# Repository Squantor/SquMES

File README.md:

# SquMES (Squantor Modular Electronics System)
This repository contains a modular system for electronics projects. 
This system comprises of a backplane and some modules, the modules are inserted into the backplane. Instead of the [ModEleSys](https://github.com/Squantor/ModEleSys) where everything is horizontal, the SquMES is vertical, this makes the backplane not so big and a bit more space efficient but the modules also have more PCB surface allowing more complex projects.

WARNING: This is still a work in progress, check back later if you are interested.

## Structure
* [electronics](electronics/README.md) contains electronics schematics and PCB drawings using Kicad
* [mechanical](mechanical/README.md) contains all the CAD drawings, mostly 3d printable objects.
* [documentation](documentation/README.md) contains more in depth information and examples using this system.
## Cloning
This repository makes use of submodules, use ```git clone --recurse-submodules https://github.com/Squantor/generic_project_template.git``` to clone everything in one go.

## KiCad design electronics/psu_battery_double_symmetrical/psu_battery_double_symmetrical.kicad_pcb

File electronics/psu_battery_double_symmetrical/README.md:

# SquMES Dual 9V battery symmetrical Powersupply
Simple symmetrical powersupply based on two batteries, has a low battery and power led indicator.
## TODO's
Still some things need to be done:
* Review with one night in between
* Produce at [OSHPARK](https://oshpark.com/)
* Assemble
* Test & characterise
* update Readme.md with pictures and BOM

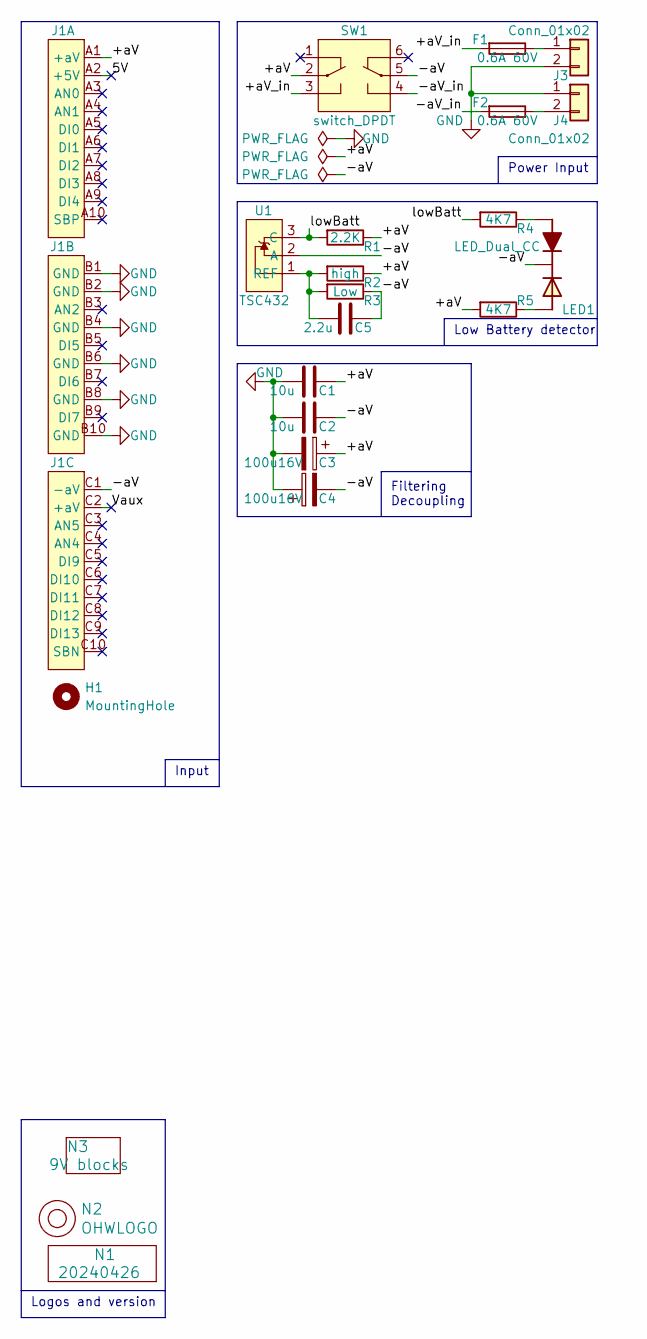
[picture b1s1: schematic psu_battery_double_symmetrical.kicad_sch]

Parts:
C1, C2: 10u; C_1206_0805
C3, C4: 100u16V; C-025-065-elco
C5: 2.2u; C_0805
F1, F2: 0.6A 60V; F_1812-bourns
H1: MountingHole; MountingHole_2.7mm_M2.5_Pad
J1: DIN41612_C3_3x10_Male_Horizontal_THT
J3, J4: Conn_01x02; JST_XH_B2B-XH-A_1x02_P2.50mm_Vertical
LED1: LED_Dual_CC; LED_DUAL_TH245_90deg
N1: 20240426; Label_Generic
N2: OHWLOGO; OSHW-Symbol_6.7x6mm_SilkScreen
N3: 9V blocks; battery_holder_9v_stacked
R1: 2.2K; R_0603_hand
R2: high; R_0603_hand
R3: Low; R_0603_hand
R4, R5: 4K7; R_0603_hand
SW1: switch_DPDT; PS-22F02
U1: TSC432; TO-92L_Inline_Wide

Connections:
/5V: J1.A2 (+5V)
/+aV: C1.2, C3.1, J1.A1 (+aV), R1.1, R2.1, R5.2, SW1.2 (SW1_C1)
/+aV_in: F1.2, SW1.3 (SW1_P2)
/-aV: C2.2, C4.2, C5.2, J1.C1 (-aV), LED1.2 (C), R3.1, SW1.5 (SW2_C1), U1.2 (A)
/-aV_in: F2.2, SW1.4 (SW2_P2)
/Vaux: J1.C2 (+aV)
/lowBatt: R1.2, R4.2, U1.3 (C)
GND: C1.1, C2.1, C3.2, C4.1, J1.B1 (GND), J1.B2 (GND), J1.B4 (GND), J1.B6 (GND), J1.B8 (GND), J1.B10 (GND), J3.2, J4.1
unnamed: F1.1, J3.1
unnamed: F2.1, J4.2
unnamed: LED1.1 (A1), R4.1
unnamed: LED1.3 (A2), R5.1
unnamed: C5.1, R2.2, R3.2, U1.1 (REF)

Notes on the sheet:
Filtering Decoupling
Input
Logos and version
Power Input
Low Battery detector

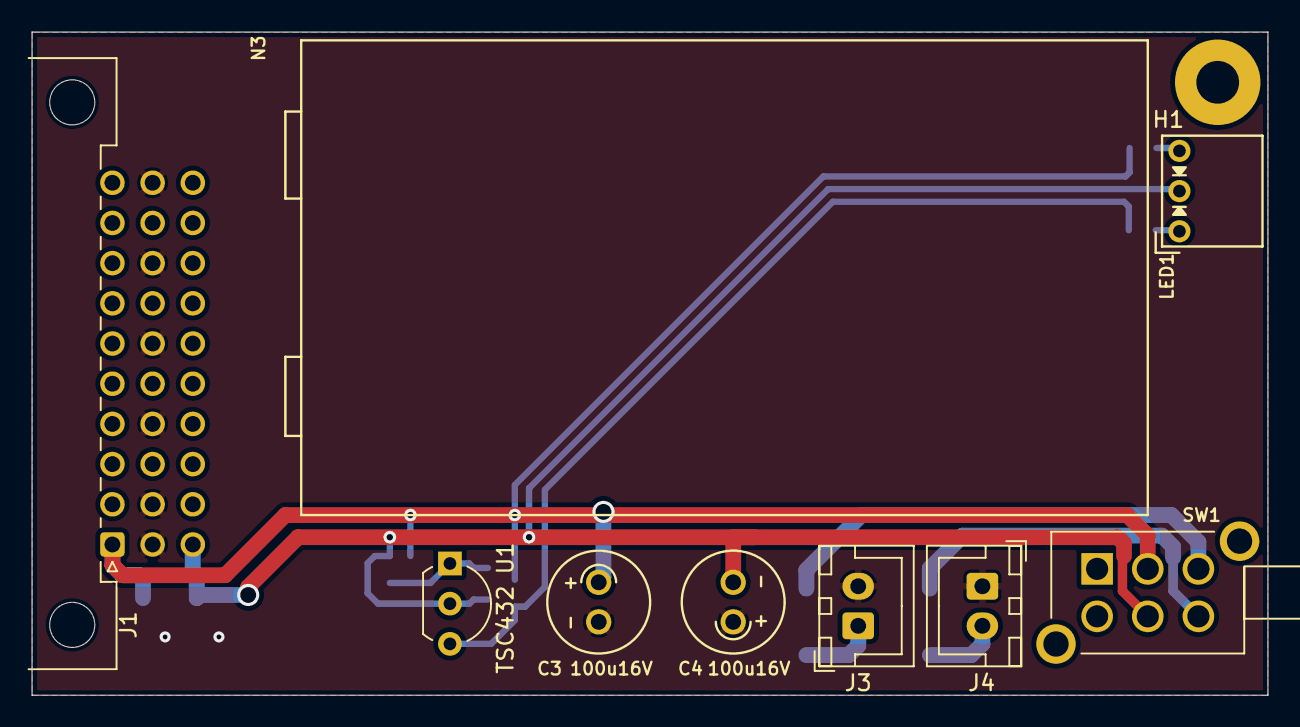
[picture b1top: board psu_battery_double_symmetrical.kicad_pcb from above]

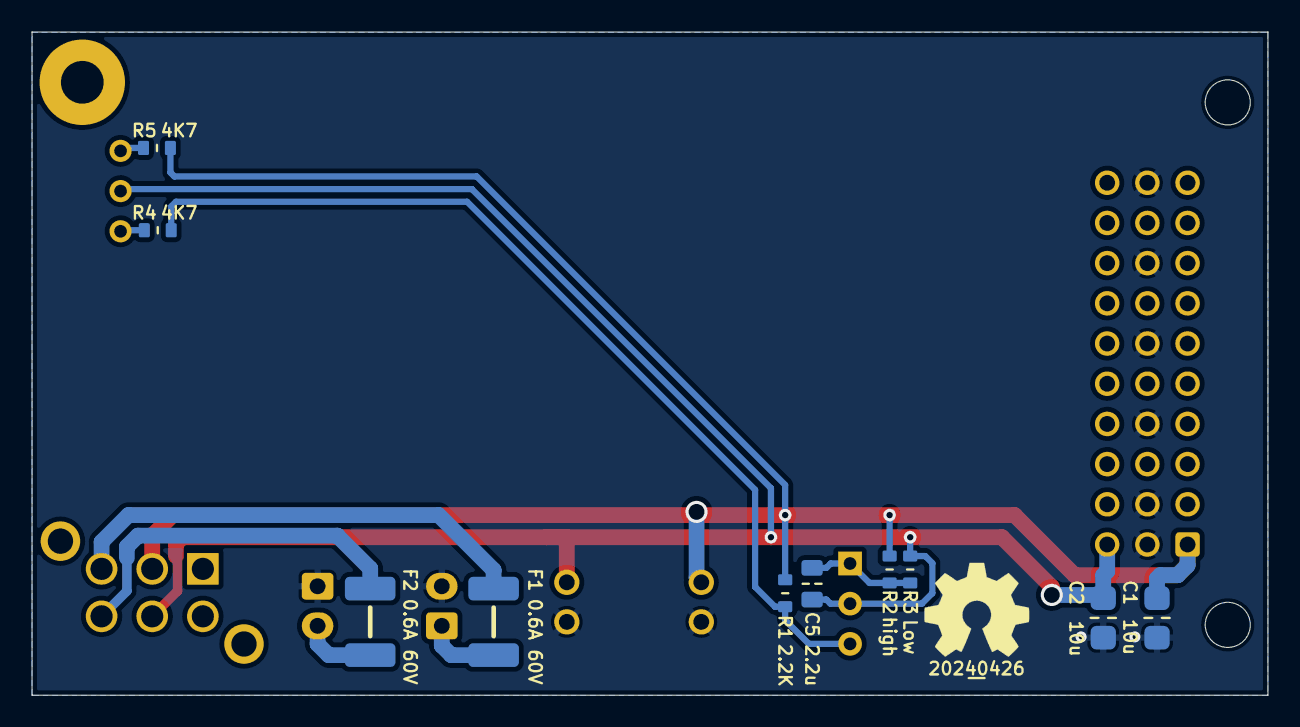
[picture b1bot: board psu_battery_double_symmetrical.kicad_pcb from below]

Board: 2 copper layers, 78.1 x 41.9 mm, 22 parts (12 on the bottom side), 11 nets.

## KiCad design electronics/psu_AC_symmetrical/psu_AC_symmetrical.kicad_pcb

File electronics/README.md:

# SquMES electronics
The backplanes and modules of the ModEleSys are stored here.
Backplanes are prefixed with ```bp``` and some extra description.
Mmodules are prefixed with ```mod``` and size in the form of ```W?``` where ? would be the size indicator. For example ```mod_W2_PSU_symmetrical``` is a module of 2 width units that contains a symmetric powersupply. One width unit is 14mm.
## Backplanes
* 30 pin DIN 41612 connector backplane for 10x10x5 cm extruded aluminium boxes
* 30 pin DIN 41612 connector backplane for larger cm extruded aluminium boxes
* 48 pin DIN 41612 connector backplane for larger aluminium boxes
* 48 pin DIN 41612 connector backplane for 2U box
## Modules
* Powersupply fed by one DC jack that provides symmetrical voltage rails and one logic supply using LD1117 LDO's
* LPC812 microcontroller board with USB to serial UART
* STM32G031 microcontroller board with USB to serial UART
* 22bit low speed ADC board
* 16bit high speed ADC board

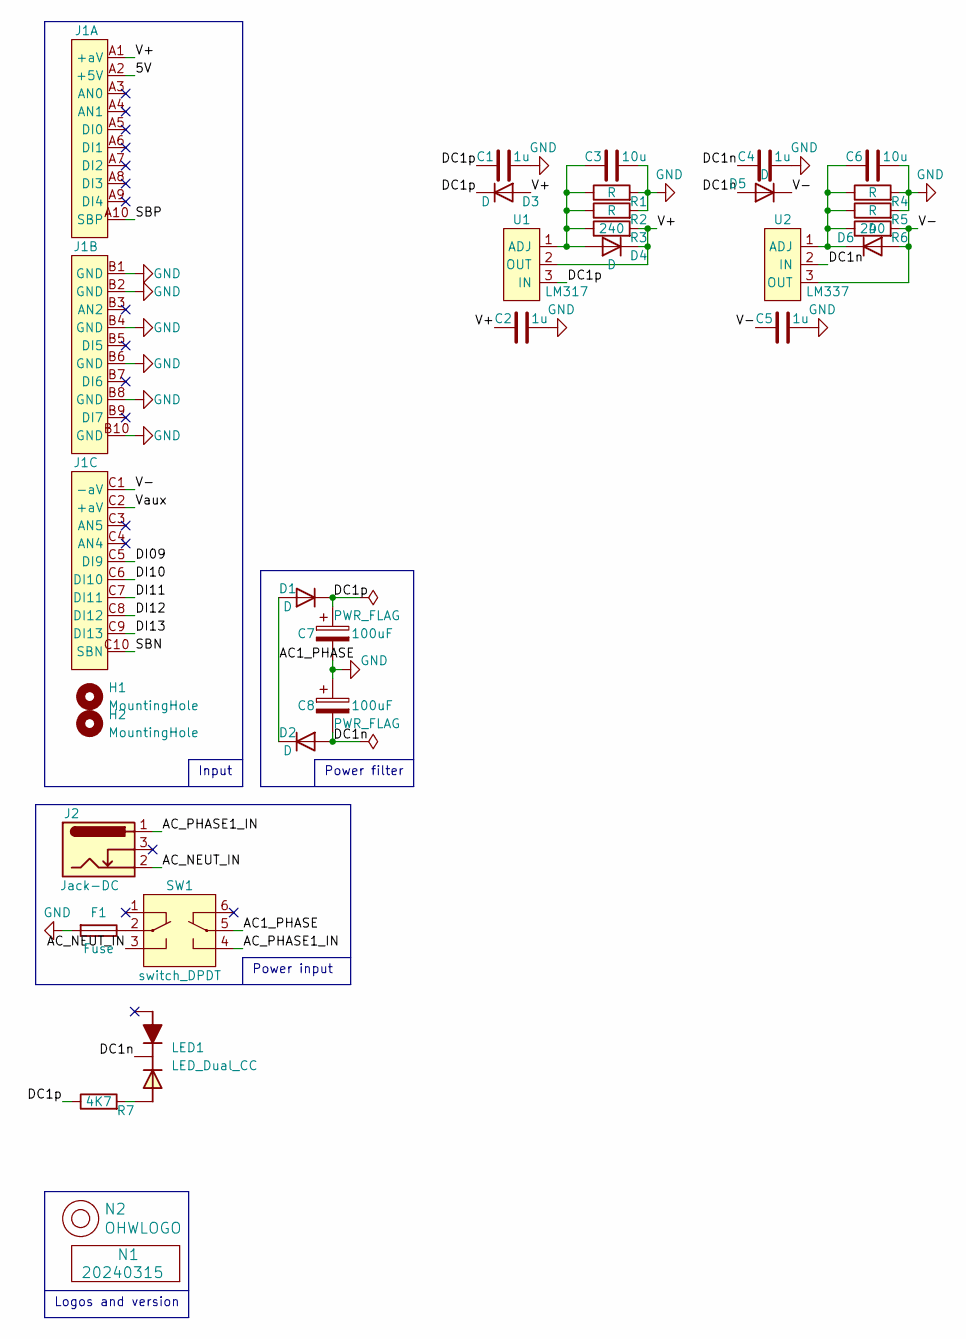
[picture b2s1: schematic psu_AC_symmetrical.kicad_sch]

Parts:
C1, C2, C4, C5: 1u; C_0805+0603
C3, C6: 10u; C_0805+0603
C7, C8: 100uF; C-050-100-elco-lying
D1, D2, D3, D5: D; SOD-123F-hand
D4, D6: D; SOD-323-nexperia-hand
F1: Fuse; F_1812-bourns
H1, H2: MountingHole; MountingHole_2.7mm_M2.5_Pad
J1: DIN41612_C3_3x10_Male_Horizontal_THT
J2: Jack-DC; BarrelJack_Horizontal_Holed
LED1: LED_Dual_CC; LED_DUAL_TH245_90deg
N1: 20240315; Label_Generic
N2: OHWLOGO; OSHW-Symbol_6.7x6mm_SilkScreen
R1, R2, R4, R5: R; R_0805+0603
R3, R6: 240; R_0805+0603
R7: 4K7; R_0805+0603
SW1: switch_DPDT; PS-22F02
U1: LM317; TO-252_D-PAK_IRF
U2: LM337; TO-252_D-PAK_IRF

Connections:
/5V: J1.A2 (+5V)
/AC1_PHASE: D1.2 (A), D2.1 (K), SW1.5 (SW2_C1)
/AC_NEUT_IN: J2.2, SW1.3 (SW1_P2)
/AC_PHASE1_IN: J2.1, SW1.4 (SW2_P2)
/DC1n: C4.1, C8.2, D2.2 (A), D5.2 (A), LED1.2 (C), U2.2 (IN)
/DC1p: C1.1, C7.1, D1.1 (K), D3.1 (K), R7.1, U1.3 (IN)
/DI09: J1.C5 (DI9)
/DI10: J1.C6 (DI10)
/DI11: J1.C7 (DI11)
/DI12: J1.C8 (DI12)
/DI13: J1.C9 (DI13)
/SBN: J1.C10 (SBN)
/SBP: J1.A10 (SBP)
/V+: C2.1, D3.2 (A), D4.1 (K), J1.A1 (+aV), R3.2, U1.2 (OUT)
/V-: C5.1, D5.1 (K), D6.2 (A), J1.C1 (-aV), R6.2, U2.3 (OUT)
/Vaux: J1.C2 (+aV)
GND: C1.2, C2.2, C3.2, C4.2, C5.2, C6.2, C7.2, C8.1, F1.2, J1.B1 (GND), J1.B2 (GND), J1.B4 (GND), J1.B6 (GND), J1.B8 (GND), J1.B10 (GND), R1.2, R2.2, R4.2, R5.2
unnamed: C3.1, D4.2 (A), R1.1, R2.1, R3.1, U1.1 (ADJ)
unnamed: C6.1, D6.1 (K), R4.1, R5.1, R6.1, U2.1 (ADJ)
unnamed: LED1.3 (A2), R7.2
unnamed: F1.1, SW1.2 (SW1_C1)

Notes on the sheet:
Input
Logos and version
Power filter
Power input

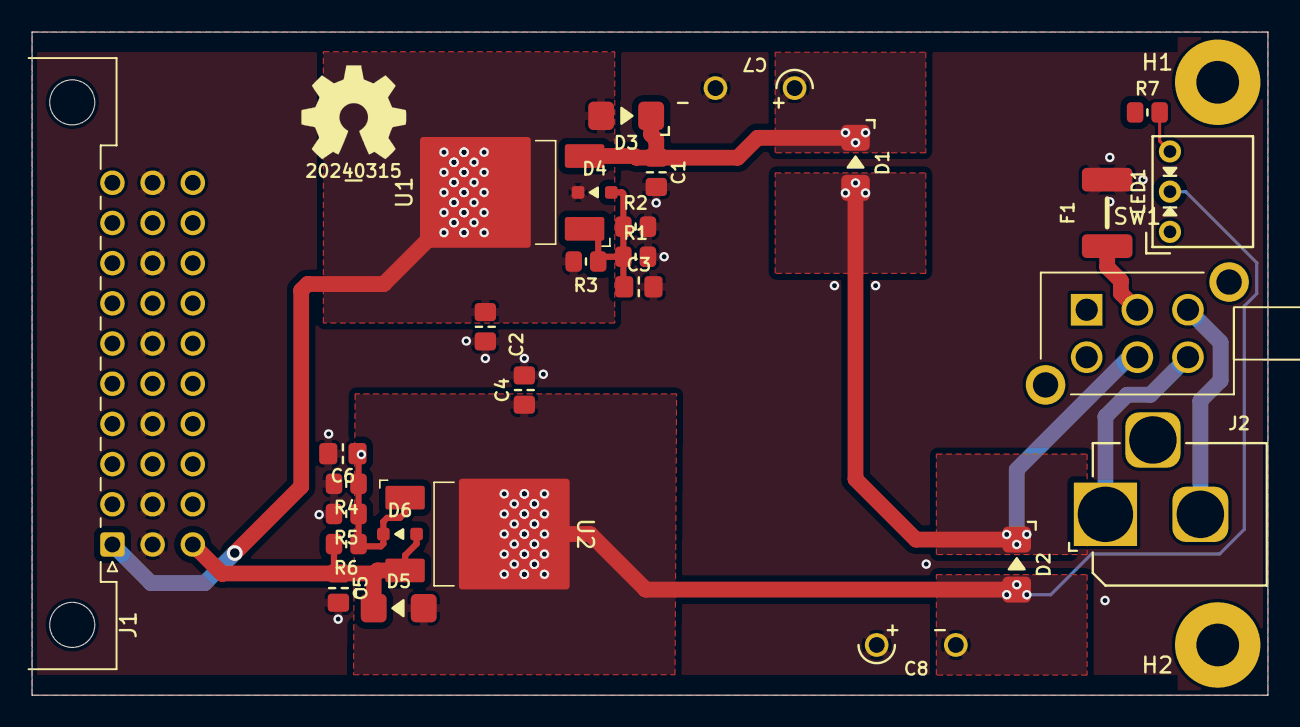
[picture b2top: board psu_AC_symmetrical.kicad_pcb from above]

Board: 2 copper layers, 78.1 x 41.9 mm, 32 parts (0 on the bottom side), 12 nets.

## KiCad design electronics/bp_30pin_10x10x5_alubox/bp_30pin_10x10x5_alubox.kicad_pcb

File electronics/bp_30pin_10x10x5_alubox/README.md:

# SquMES 30 pin backplane for 10x10x5cm sized extruded aluminium boxes
Backplane for 10x10x5cm extruded aluminium boxes with 30 pin DIN 41612 connectors. Contains space for 4W modules, three 2W and one 1W module.
TODO, link to drill guide for backplate and other mechanical components.
## TODO's
Still some things need to be done:
* schematic entry 
* PCB layout
* Review with one night in between
* Produce at [OSHPARK](https://oshpark.com/)
* Assemble
* Test & characterise
* update Readme.md with pictures and BOM
## BOM
This is a list of hardware components. If just mentioned a generic component like a 1K 0402 resistor, just name it as such, free to substitute. If you need some special integrated IC's show some sources like Mouser, Digikey, Farnell, or LCSC
* 30 pin male DIN41621 connector [LCSC](https://www.lcsc.com/product-detail/Mezzanine-Connectors-Board-to-Board_JILN-3511330AMSS0BNA1_C963712.html) or [Reichelt](https://www.reichelt.nl/nl/nl/d-sub-connector-30-pins-recht-4mm-a-b-c-ml-r3-30g4-p36310.html)
* M2.5 mounting material (TODO links to nindejin on aliexpress)
## Pictures
TODO

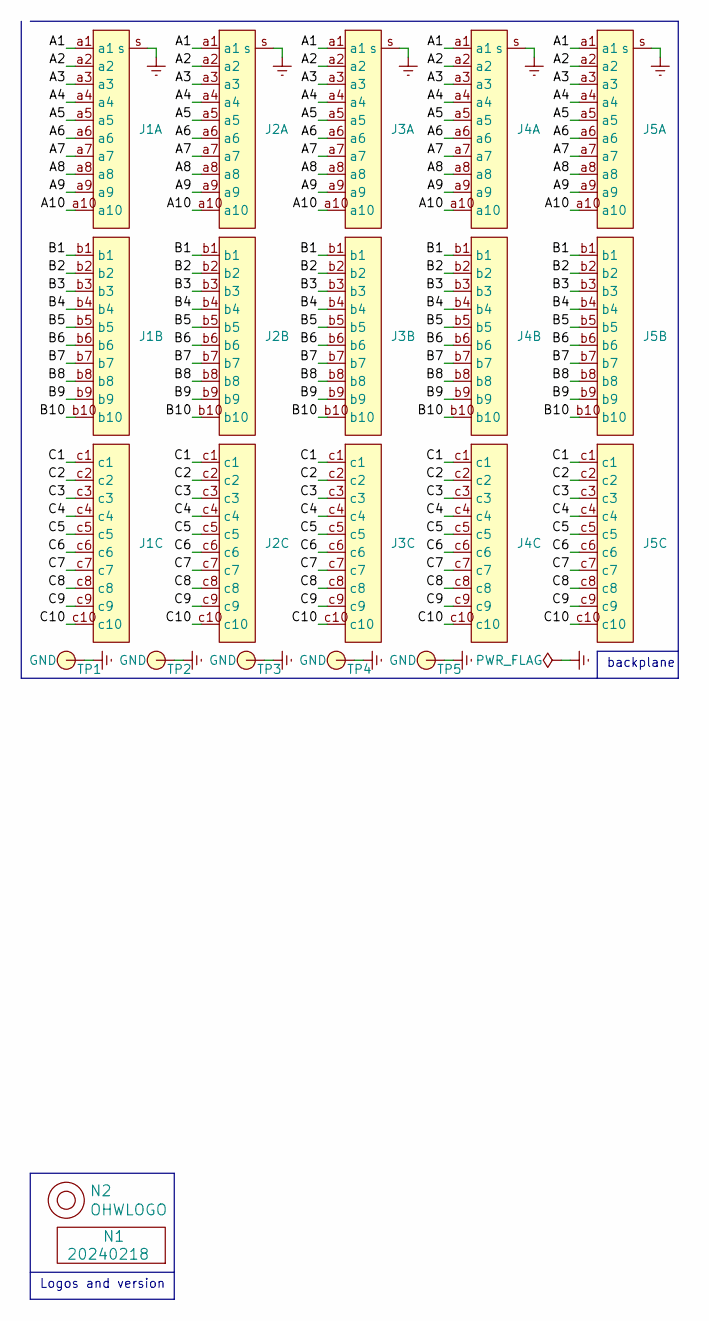
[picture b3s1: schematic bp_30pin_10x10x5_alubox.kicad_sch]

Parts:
J1, J2, J3, J4, J5: DIN41612_R3_3x10_Male_Vertical_THT_shield
N1: 20240218; Label_Generic
N2: OHWLOGO; OSHW-Symbol_6.7x6mm_SilkScreen
TP1, TP2, TP3, TP4, TP5: GND; TestPoint_hole_H05R10

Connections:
/A1: J1.a1, J2.a1, J3.a1, J4.a1, J5.a1
/A2: J1.a2, J2.a2, J3.a2, J4.a2, J5.a2
/A3: J1.a3, J2.a3, J3.a3, J4.a3, J5.a3
/A4: J1.a4, J2.a4, J3.a4, J4.a4, J5.a4
/A5: J1.a5, J2.a5, J3.a5, J4.a5, J5.a5
/A6: J1.a6, J2.a6, J3.a6, J4.a6, J5.a6
/A7: J1.a7, J2.a7, J3.a7, J4.a7, J5.a7
/A8: J1.a8, J2.a8, J3.a8, J4.a8, J5.a8
/A9: J1.a9, J2.a9, J3.a9, J4.a9, J5.a9
/A10: J1.a10, J2.a10, J3.a10, J4.a10, J5.a10
/B1: J1.b1, J2.b1, J3.b1, J4.b1, J5.b1
/B2: J1.b2, J2.b2, J3.b2, J4.b2, J5.b2
/B3: J1.b3, J2.b3, J3.b3, J4.b3, J5.b3
/B4: J1.b4, J2.b4, J3.b4, J4.b4, J5.b4
/B5: J1.b5, J2.b5, J3.b5, J4.b5, J5.b5
/B6: J1.b6, J2.b6, J3.b6, J4.b6, J5.b6
/B7: J1.b7, J2.b7, J3.b7, J4.b7, J5.b7
/B8: J1.b8, J2.b8, J3.b8, J4.b8, J5.b8
/B9: J1.b9, J2.b9, J3.b9, J4.b9, J5.b9
/B10: J1.b10, J2.b10, J3.b10, J4.b10, J5.b10
/C1: J1.c1, J2.c1, J3.c1, J4.c1, J5.c1
/C2: J1.c2, J2.c2, J3.c2, J4.c2, J5.c2
/C3: J1.c3, J2.c3, J3.c3, J4.c3, J5.c3
/C4: J1.c4, J2.c4, J3.c4, J4.c4, J5.c4
/C5: J1.c5, J2.c5, J3.c5, J4.c5, J5.c5
/C6: J1.c6, J2.c6, J3.c6, J4.c6, J5.c6
/C7: J1.c7, J2.c7, J3.c7, J4.c7, J5.c7
/C8: J1.c8, J2.c8, J3.c8, J4.c8, J5.c8
/C9: J1.c9, J2.c9, J3.c9, J4.c9, J5.c9
/C10: J1.c10, J2.c10, J3.c10, J4.c10, J5.c10
Earth: J1.s, J2.s, J3.s, J4.s, J5.s, TP1.1, TP2.1, TP3.1, TP4.1, TP5.1

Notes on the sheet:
Logos and version
backplane

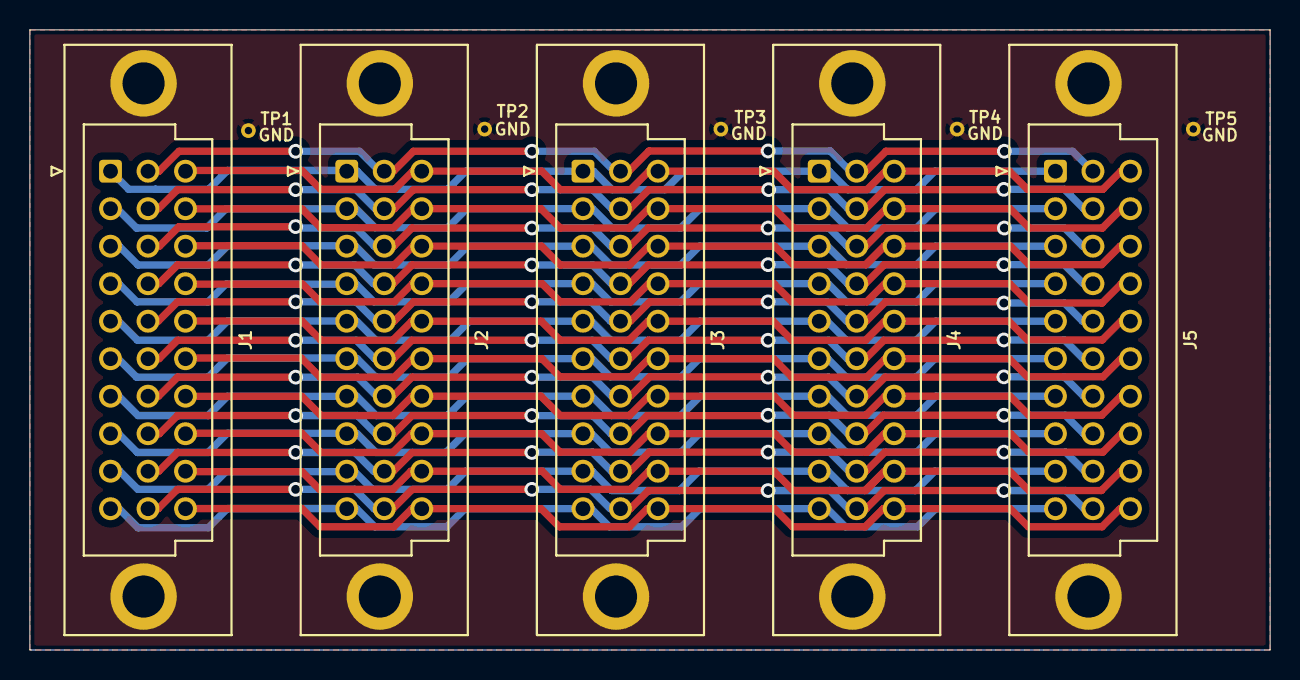
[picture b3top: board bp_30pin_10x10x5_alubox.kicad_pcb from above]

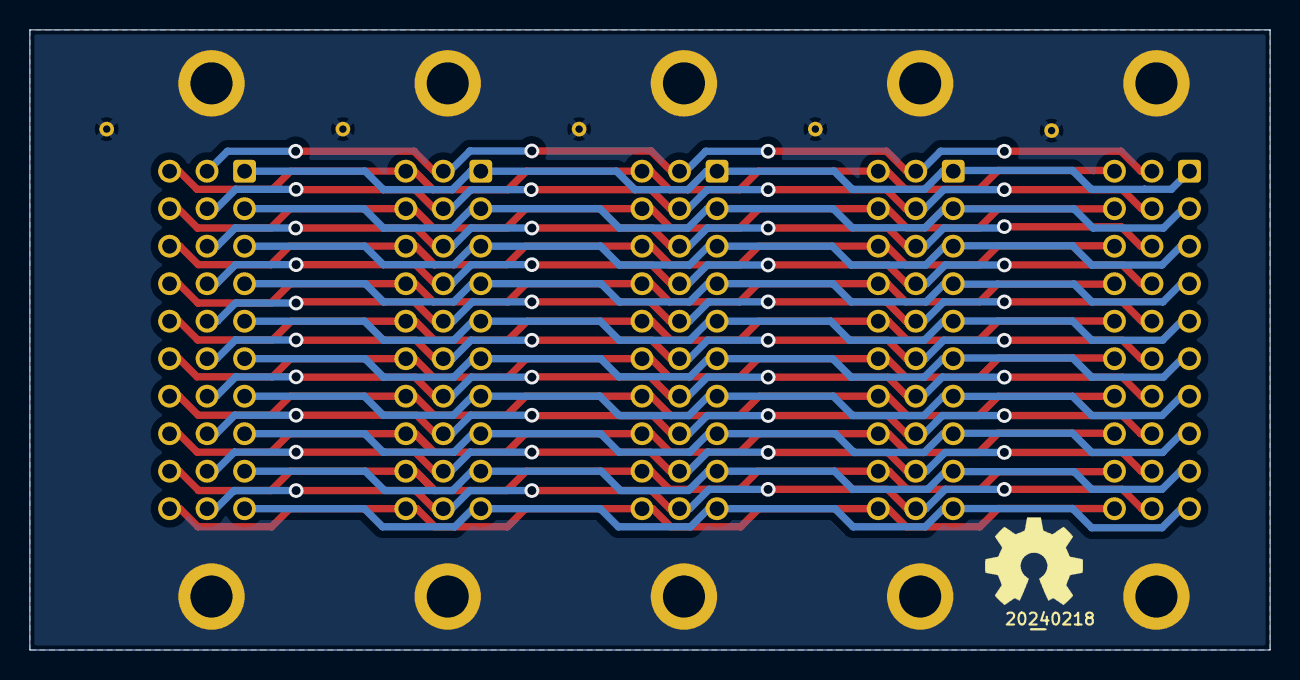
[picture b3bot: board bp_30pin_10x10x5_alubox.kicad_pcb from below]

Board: 2 copper layers, 84.0 x 42.0 mm, 12 parts (2 on the bottom side), 31 nets.

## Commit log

2023-09-17 initial population
2023-09-17 added inital 30 pin backplane
2023-09-17 added lock files to gitignore, WIP 30 pin backplane
2023-09-17 Place and route done
2023-12-04 updated PCB library
2023-12-04 updated versionnumber, added block for backplane, larger copper plane spacing
2023-12-08 updated board to Aisler Budget design rules, fixed DRC errors
2023-12-08 removed one connector to give a 16mm pitch for the modules, one module will be a bit small cramped
2024-01-11 updated backplane to new components
2024-02-18 prepared for production
2024-03-15 started with symmetrical and asymmetrical AC supplies
2024-04-24 symmetrical double supply PSU
2024-04-25 review done
2024-04-26 prepared for production minor updates
